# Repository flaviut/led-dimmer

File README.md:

# IoT RGBWW strip dimmer

Designed for use with ESPHome, this project is a compact & powerful dimmer for all LED strips. The primary goal was low cost, in the most compact package possible. For scale, the picture above was taken on a 1 inch grid.

This is intended as a substitute for the poorly-designed Magic Home LED strip controllers.

Note: the yellow wire in the photo does not work as a capacitive touch sensor, that was a failed experiment.

## Features

- Up to 5 lighting channels
- Support for voltages between 5V and 24V
- Up to 4A per channel. Outputs can be paralleled.
- Reasonable efficiency: approx. 200mW standby power draw.
- Low cost, PCB is about $6/ea manufactured at qty 10, or about $4.30/ea at qty 30.

## Description

[Schematic](./docs/schematic.pdf)

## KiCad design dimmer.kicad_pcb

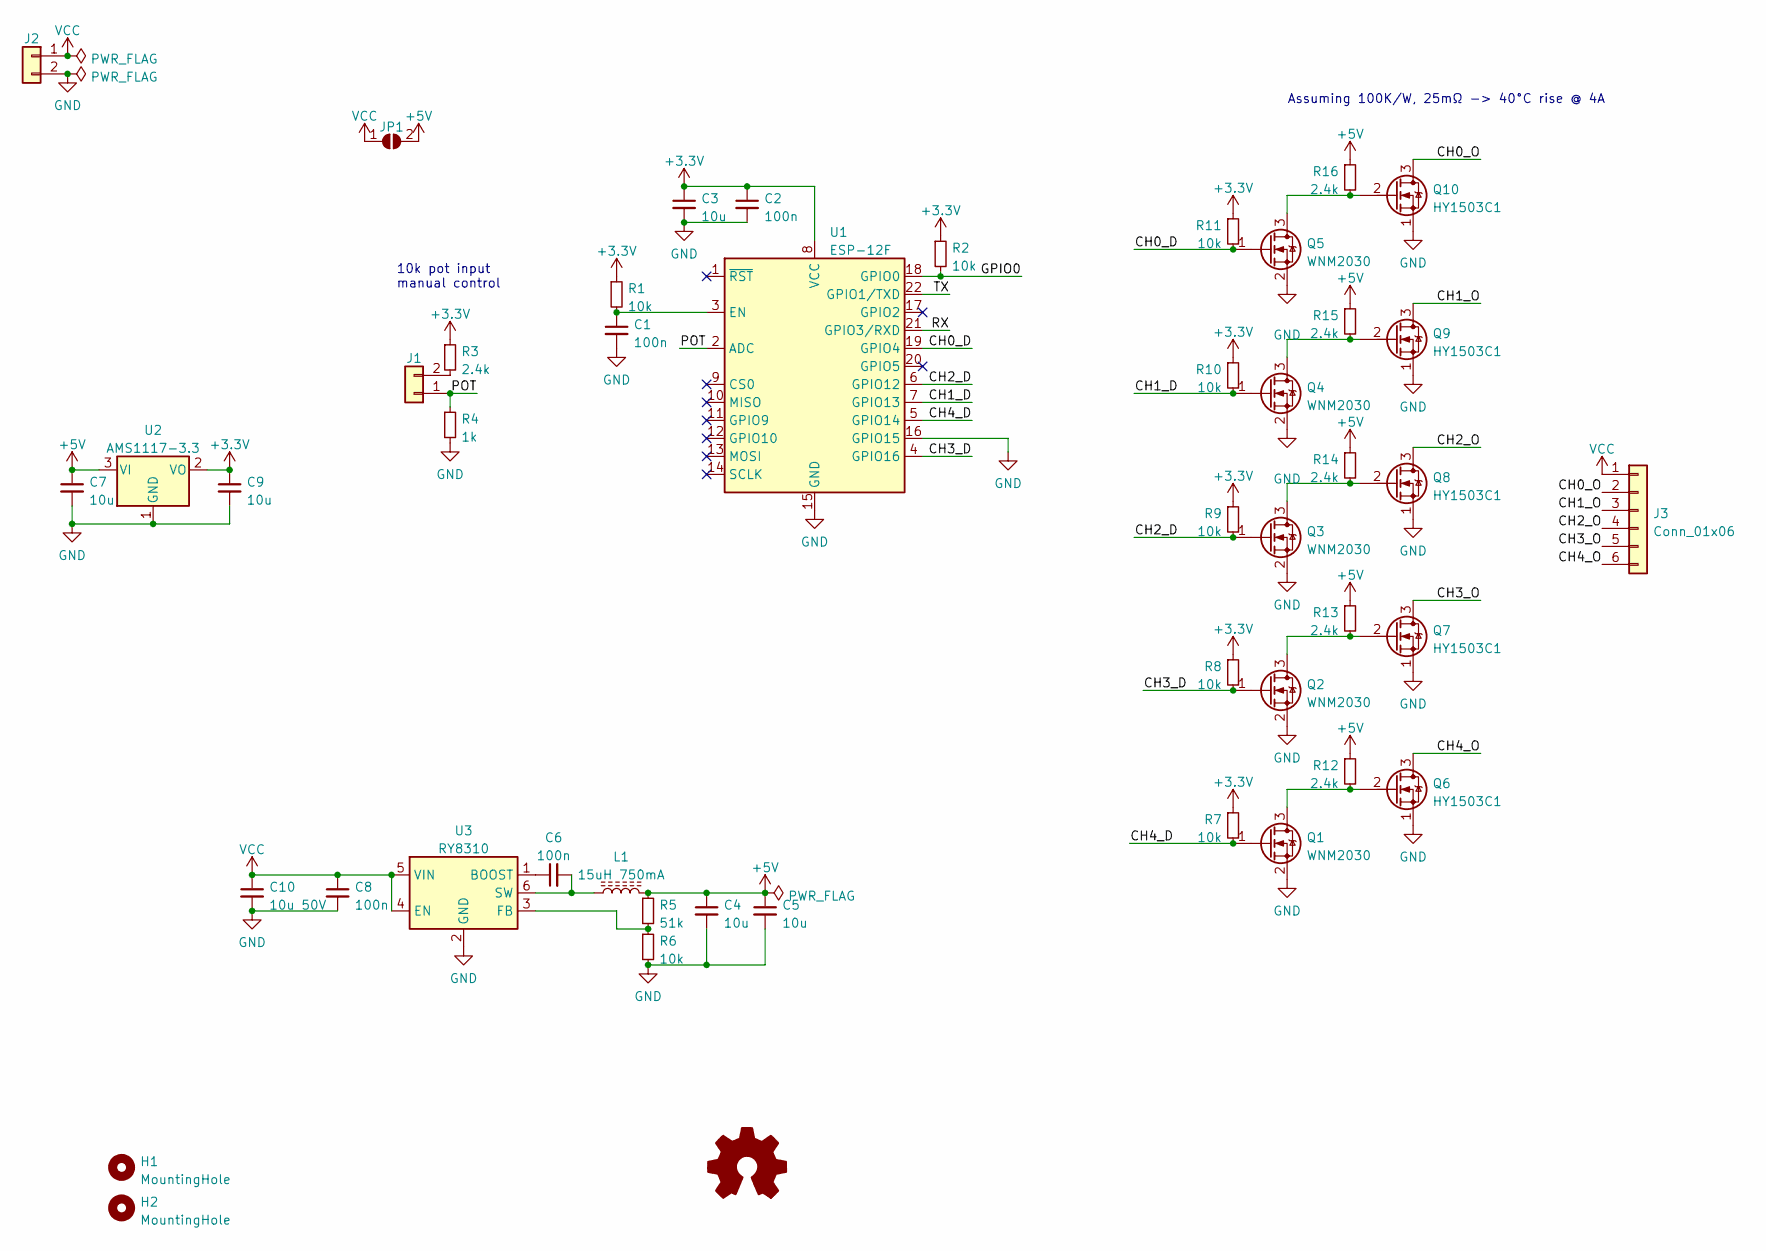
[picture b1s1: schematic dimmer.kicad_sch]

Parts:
C1, C2, C6, C8: 100n; C_0402_1005Metric; LCSC C307331
C3, C4, C5, C7, C9: 10u; C_0402_1005Metric; LCSC C15525
C10: 10u 50V; C_0805_2012Metric; LCSC C440198
H1, H2: MountingHole; ToolingHole
J1: Conn_01x02; PinHeader_1x02_P2.54mm_Vertical
J2: Conn_01x02; SolderWire-0.75sqmm_1x02_P4.8mm_D1.25mm_OD2.3mm
J3: Conn_01x06; PinHeader_1x06_P2.54mm_Horizontal
JP1: SolderJumper_2_Open; SolderJumper-2_P1.3mm_Open_TrianglePad1.0x1.5mm
L1: 15uH 750mA; L_Bourns-SRN4018; LCSC C167837
LOGO1: Logo_Open_Hardware_Small; OSHW-Logo2_7.3x6mm_SilkScreen
Q1, Q2, Q3, Q4, Q5: WNM2030; SOT-723; LCSC C239769
Q6, Q7, Q8, Q9, Q10: HY1503C1; DFN-8-1EP_3x3mm_P0.65mm_EP2x2.4mm; LCSC C315567
R1, R2, R6, R7, R8, R9, R10, R11: 10k; R_0402_1005Metric; LCSC C25744
R3, R12, R13, R14, R15, R16: 2.4k; R_0402_1005Metric; LCSC C25882
R4: 1k; R_0402_1005Metric; LCSC C11702
R5: 51k; R_0402_1005Metric; LCSC C25794
U1: ESP-12F; ESP-12E; LCSC C82891
U2: AMS1117-3.3; SOT-223-3_TabPin2; LCSC C6186
U3: RY8310; TSOT-23-6; LCSC C370876

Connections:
+3.3V: C2.1, C3.1, C9.1, R1.1, R2.1, R3.1, R7.1, R8.1, R9.1, R10.1, R11.1, U1.8 (VCC), U2.2 (VO)
+5V: C4.1, C5.1, C7.1, JP1.2 (B), L1.2, R5.1, R12.1, R13.1, R14.1, R15.1, R16.1, U2.3 (VI)
/CH0_D: Q5.1 (G), R11.2, U1.19 (GPIO4)
/CH0_O: J3.2, Q10.3 (D)
/CH1_D: Q4.1 (G), R10.2, U1.7 (GPIO13)
/CH1_O: J3.3, Q9.3 (D)
/CH2_D: Q3.1 (G), R9.2, U1.6 (GPIO12)
/CH2_O: J3.4, Q8.3 (D)
/CH3_D: Q2.1 (G), R8.2, U1.4 (GPIO16)
/CH3_O: J3.5, Q7.3 (D)
/CH4_D: Q1.1 (G), R7.2, U1.5 (GPIO14)
/CH4_O: J3.6, Q6.3 (D)
/GPIO0: R2.2, U1.18 (GPIO0)
/POT: J1.1, R4.1, U1.2 (ADC)
/RX: U1.21 (GPIO3/RXD)
/TX: U1.22 (GPIO1/TXD)
GND: C1.2, C2.2, C3.2, C4.2, C5.2, C7.2, C8.2, C9.2, C10.2, J2.2, Q1.2 (S), Q2.2 (S), Q3.2 (S), Q4.2 (S), Q5.2 (S), Q6.1 (S), Q7.1 (S), Q8.1 (S), Q9.1 (S), Q10.1 (S), R4.2, R6.2, U1.15 (GND), U1.16 (GPIO15), U2.1 (GND), U3.2 (GND)
unnamed: C1.1, R1.2, U1.3 (EN)
unnamed: C6.1, U3.1 (BOOST)
unnamed: C6.2, L1.1, U3.6 (SW)
unnamed: J1.2, R3.2
unnamed: Q1.3 (D), Q6.2 (G), R12.2
unnamed: Q2.3 (D), Q7.2 (G), R13.2
unnamed: Q3.3 (D), Q8.2 (G), R14.2
unnamed: Q4.3 (D), Q9.2 (G), R15.2
unnamed: Q5.3 (D), Q10.2 (G), R16.2
unnamed: R5.2, R6.1, U3.3 (FB)
VCC: C8.1, C10.1, J2.1, J3.1, JP1.1 (A), U3.4 (EN), U3.5 (VIN)

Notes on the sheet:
Assuming 100K/W, 25mΩ -> 40°C rise @ 4A
10k pot input manual control

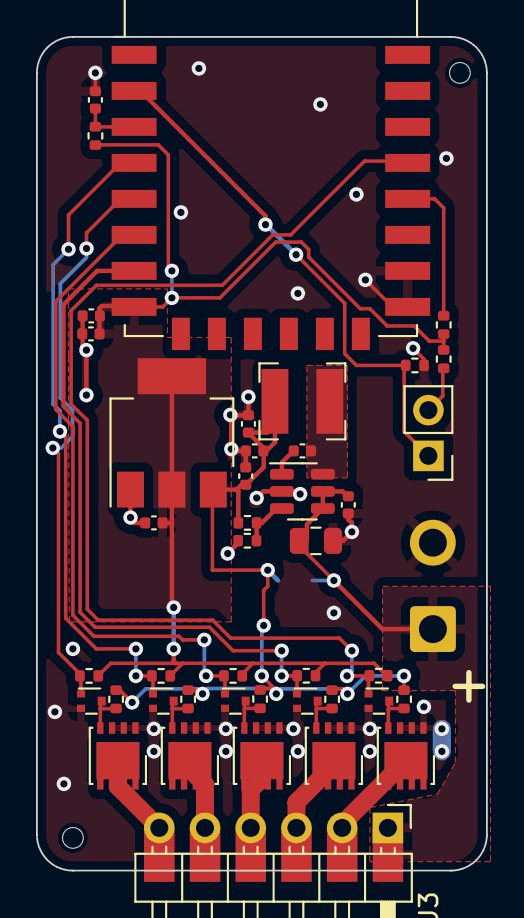
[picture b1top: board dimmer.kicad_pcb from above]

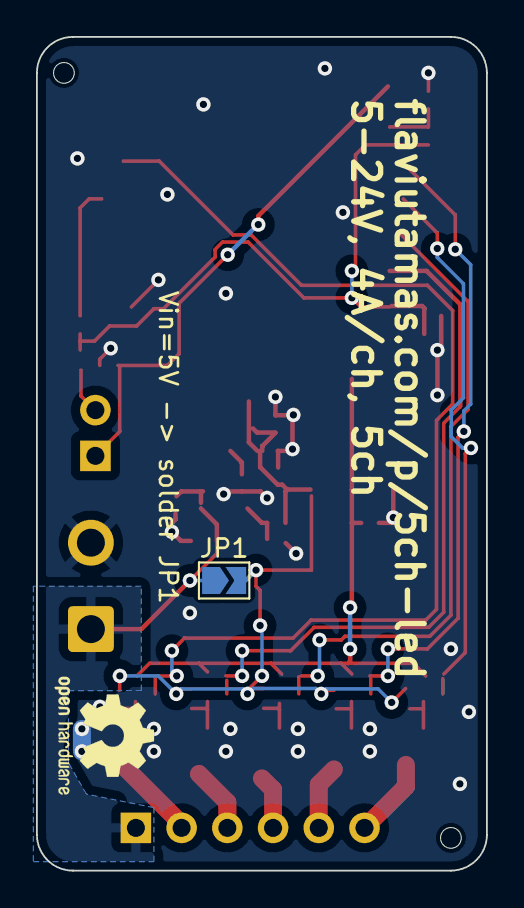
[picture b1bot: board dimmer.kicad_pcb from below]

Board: 2 copper layers, 25.0 x 46.3 mm, 47 parts (2 on the bottom side), 26 nets.

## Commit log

2022-04-03 Switch to buck & go to production!
2022-07-02 Simplify design
2022-07-02 Add kibot
2022-07-02 reannotate
2022-07-17 Remove extra LCSC Part property
2022-07-17 Add readme
2022-07-25 Update for in-stock parts
2022-07-25 Add github workflow
2022-07-29 Disconnect CH0 from on-board LED
2022-07-29 Increase 3.3V regulator pad size
2022-07-29 Add tooling holes
2025-11-02 add docs
2025-11-02 update ci
2025-11-02 fix ci?
2025-11-02 fix ci
2025-11-02 update cost
